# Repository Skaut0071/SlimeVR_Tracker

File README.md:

# SlimeVR DIY Project

## Overview
This is a DIY project based on the official SlimeVR documentation. The design is created for educational and hobbyist purposes.

### Visuals
<h2 align="center"><b>Front side:</b></h2>

<h2 align="center"><b>Back side:</b></h2>

<h2 align="center"><b>Case:</b></h2>

## Project Information
- **KiCad Version:** 9.0
- **PCB Version:** 3W + 2.6WE (older *bigger* board files are saved if you want them *Version 0.7*, *Version 0.9* and *Version 2.5W*)

  > *W:* = Wireless
  
  > *E:* = Extension

- **Schematic Version:** 2.0
- **Project Type:** DIY/Hobby
- **Manufacture:** JLCPCB

### Hardware Specifications
- **MCU:** ESP32C3 WROOM 02
- **Supported IMU:** Any with same pin out as BMI160 module (*reference at end*)
- **Battery Management:** Integrated TP4056 charging circuit
- **Features:** Battery monitoring (Firmware), Power switch, Status LEDs

### Firmware
- *Will be available when fully tested as functional*

## Disclaimer
⚠️ **Functionality is not guaranteed.** This is an experimental project and may contain errors or issues. Use at your own risk.
- Also there can be a few grafical and speling mistakes so be aware of it.
- The images are for reference only until new version arrives, I will make new ones after

## Design Files
- PCB layout and schematic files are included in this repository
- Based on official SlimeVR documentation and specifications

## Bill of Materials (BOM)
Detailed interactive list of components:
👉 **[Open Interactive BOM (ibom.html)](https://skaut0071.github.io/SlimeVR_Tracker/PDFs/ibom)**

## Contributing
Feel free to submit issues, suggestions, or improvements via GitHub issues or pull requests.

## References
- [Official SlimeVR Documentation](https://docs.slimevr.dev/)
- [SlimeVR GitHub](https://github.com/SlimeVR)
- [BMI160 Module](https://www.aliexpress.com/item/1005006351402967.html)

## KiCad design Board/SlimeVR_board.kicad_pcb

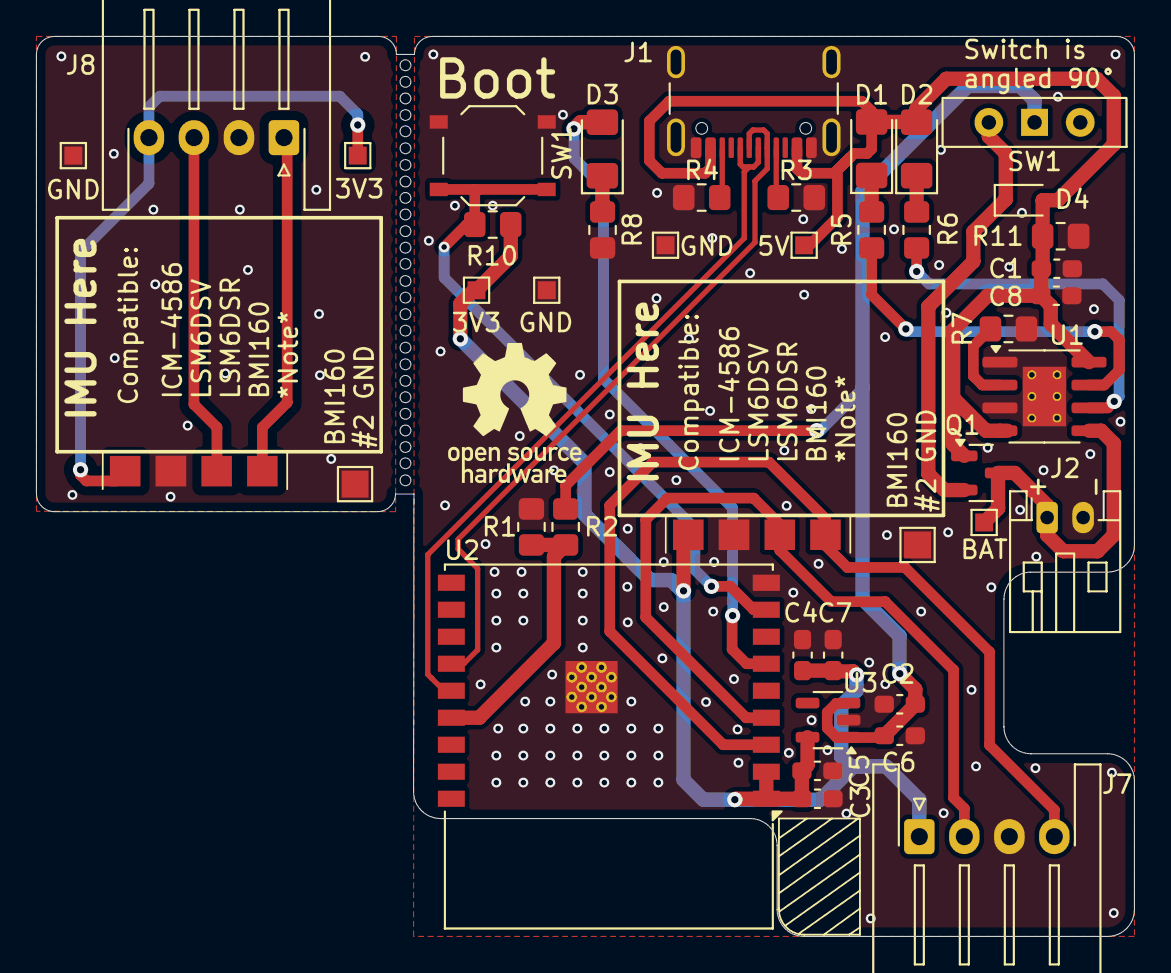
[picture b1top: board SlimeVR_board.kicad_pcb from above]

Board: 2 copper layers, 61.0 x 50.0 mm, 43 parts (0 on the bottom side), 21 nets.

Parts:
3V3, 3V3#2, 5V: TestPoint_Pad_1.0x1.0mm
BAT: TestPoint_Pad_1.0x1.0mm
BMI160
#2 GND, BMI160
#2 GND#2: TestPoint_Pad_1.5x1.5mm
C1, C2, C4, C5: 100nF; C_0603_1608Metric_Pad1.08x0.95mm_HandSolder
C3, C7: 10uF; C_0603_1608Metric_Pad1.08x0.95mm_HandSolder
C6, C8: 1uF; C_0603_1608Metric_Pad1.08x0.95mm_HandSolder
D1: FYLS-1206URC; LED_1206_3216Metric_Pad1.42x1.75mm_HandSolder
D2: FYLS-1206PGC; LED_1206_3216Metric_Pad1.42x1.75mm_HandSolder
D3: FYLS-1206UWC; LED_1206_3216Metric_Pad1.42x1.75mm_HandSolder
D4: 1N4007WS; D_SOD-323
GND: TestPoint_Pad_1.0x1.0mm
GND#2, GND#3: TestPoint_Pad_1.0x1.0mm
J1: USB_C_Receptacle_USB2.0_16P; USB_C_Receptacle_GCT_USB4105-xx-A_16P_TopMnt_Horizontal
J2: JST-PH; JST_PH_S2B-PH-K_1x02_P2.00mm_Horizontal
J3, J4: SMD_Pads; Pin_1x04_SMD_P2.54mm
J7, J8: JTX-HX-A-1; JST_XH_S4B-XH-A-1_1x04_P2.50mm_Horizontal
Q1: DMP3099L-7; SOT-23
R1, R2: 47k; R_0805_2012Metric_Pad1.20x1.40mm_HandSolder
R3, R4, R11: 5.1k; R_0805_2012Metric_Pad1.20x1.40mm_HandSolder
R5, R6, R8: 1k; R_0805_2012Metric_Pad1.20x1.40mm_HandSolder
R7: 1.2k; R_0805_2012Metric_Pad1.20x1.40mm_HandSolder
R10: 10k; R_0805_2012Metric_Pad1.20x1.40mm_HandSolder
SW1: LA215009; SW_Slide-03_Wuerth-WS-SLTV_10x2.5x6.4_P2.54mm
SW2: SW_Push; SW_Push_1P1T_XKB_TS-1187A
U1: TP4056-ESOP8; SOIC-8-1EP_3.9x4.9mm_P1.27mm_EP2.41x3.3mm_ThermalVias
U2: ESP32-C3-WROOM-02-N4; ESP32-C3-WROOM-02
U3: XC6220B331MR; SOT-23-5

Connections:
+3.3V: 3V3.1, 3V3#2.1, C3.1, C4.1, C5.1, C7.1, J3.1, J4.1, J7.1, J8.4, R10.1, U2.1 (3V3), U2.2 (EN), U3.5 (VOUT)
+5V: 5V.1, C1.1, C8.1, D1.2 (A), D2.2 (A), D4.2 (A), J1.A4 (VBUS), J1.A9 (VBUS), J1.B4 (VBUS), J1.B9 (VBUS), Q1.1 (G), R11.2, U1.4 (V_{CC}), U1.8 (CE)
+BATT: BAT.1, J2.1, Q1.3 (D), U1.5 (BAT)
Battery_sence: R1.1, R2.2, U2.15 (IO3)
D+: J1.A6 (D+), J1.B6 (D+), U2.14 (IO19)
D-: J1.A7 (D-), J1.B7 (D-), U2.13 (IO18)
Earth: BMI160 #2 GND.1, BMI160 #2 GND#2.1, C1.2, C2.2, C3.2, C4.2, C5.2, C6.2, C7.2, C8.2, GND.1, GND#2.1, GND#3.1, J1.A1 (GND), J1.A12 (GND), J1.B1 (GND), J1.B12 (GND), J1.S1 (SHIELD), J2.2, J3.2, J4.2, J7.3, J8.2, R1.2, R3.2, R4.1, R7.2, R8.1, R11.1, SW2.1, U1.1 (TEMP), U1.3 (GND), U1.9 (EPAD), U2.9 (GND), U2.19 (GND), U3.2 (GND)
unnamed: D1.1 (K), R5.1
unnamed: D2.1 (K), R6.1
unnamed: D3.2 (A), U2.6 (IO7)
unnamed: D3.1 (K), R8.2
unnamed: D4.1 (K), Q1.2 (S), SW1.1 (A)
unnamed: J1.A5 (CC1), R3.1
unnamed: J1.B5 (CC2), R4.2
unnamed: C2.1, C6.1, R2.1, SW1.2 (B), U3.1 (VIN), U3.3 (CE)
unnamed: R7.1, U1.2 (PROG)
unnamed: R5.2, U1.7 (~CHRG)
unnamed: R6.2, U1.6 (~STDBY)
unnamed: R10.2, SW2.2, U2.8 (IO9)
SCL: J3.3, J4.3, J7.2, J8.3, U2.4 (IO5)
SDA: J3.4, J4.4, J7.4, J8.1, U2.3 (IO4)

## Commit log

2025-06-07 Create LICENSE
2025-06-15 New Version
    skiped few version that ware bad or not good or not funcioning
2025-06-15 Created Custom.pretty
2025-06-15 Uploaded custom footprints
2025-06-15 Create no-pupruse
2025-06-15 Added board blueprint and material list
2025-06-15 Create no-purpuse
2025-06-15 Uploaded old PCB
2025-06-15 Create no-pupuse
2025-06-15 Uploaded 3D model
2025-07-02 New version
2025-07-02 Newest verison
2025-07-02 New older version avaible
2025-07-02 New Schematic PDF
2025-07-02 New Grep files
2025-07-02 Updated for new version
2025-07-02 Create no-purpose
2025-09-08 New version of board
    Fixex:
    - grafical issues and speling
    - wrong diode used, board wont get more then 150mA
    - battery pins has been swaped for standarizes conection
2025-09-08 New 3D models for new board
2025-09-08 New greb files for new board
2025-09-08 New PDFs for new board
2025-09-09 Fix labels
    - Fix wrong labels position at battery conetion
2025-09-13 Nweset Board update
    Update log:
    - Moved 3.3 conventor closer to esp for more stability
    - Properly labeled Boot and Reset pads with own GND
    - New and remade grafic
    - Two capacitators no more needed (material saving :D)
    - New Logo (I got some logo of my probebly will change idk)
2025-09-13 Newest board models
    (they didnt uploaded from last update)
2025-09-13 Delete 3D/SlimeVR_board.mtl
    They are not uploading so deliting then new upload
2025-09-13 Delete 3D/SlimeVR_board.obj
    same as last one...
2025-09-13 Delete 3D/SlimeVR_board.wrl
    same... I AM LAZY :D
2025-09-13 Newest board uptade
    )idk why it must be like this)
2025-09-13 Newest board update
    I am dumb, I forgot to create new models :D
2025-11-13 Update pcb and inproved a bit schematic
2025-11-13 Fix spelling and grammatical mistakes in README
    Correct spelling and grammatical errors in README.
2025-12-26 Redisign, Power Supply improved
    Removed reset pin becuse just hardware off > on
    Added physical button for boot
    HT7833 replaced for XC6220B331MR becuse HT7833 not working :(
    Small design silkscreen changes
2025-12-26 updated .gitignor for backups
2026-01-06 Reference pictures upload
2026-01-06 Rename obrázek_2026-01-06_213010303.png to Front.png
2026-01-06 Rename obrázek_2026-01-06_213046750.png to Back.png
2026-01-06 Fix formatting in README for Supported IMU section
2026-01-06 Fix link path for Interactive BOM in README
2026-01-06 Update BOM link to use GitHub Pages URL
2026-01-06 Fix formatting of BOM link in README
2026-01-06 Updated pcb
    Fixed pull up rezistor not connected
    Fixed small conection of 5V to LDO
2026-01-06 Fixed iBom
    Removed unused colum Sim.Device
2026-01-06 Enhance visuals section in README
    Updated visuals section with centered headings and images.
2026-01-07 Updated ibom
    Removed J3 and J4 references, reason not actual component
2026-01-07 Updated ibom
    Fixed row counting
2026-01-07 Updated images
2026-01-07 Add case image and enhance project details
    Added case image and updated project information.
2026-01-09 Add width and height to case image in README
    Updated image tag to include width and height attributes.
2026-01-25 3D model krabičky
2026-02-06 Adjust image height in README
    Updated image height in README for better display.

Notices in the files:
Board/SlimeVR_board.kicad_pcb:
©2025 Skaut0071
